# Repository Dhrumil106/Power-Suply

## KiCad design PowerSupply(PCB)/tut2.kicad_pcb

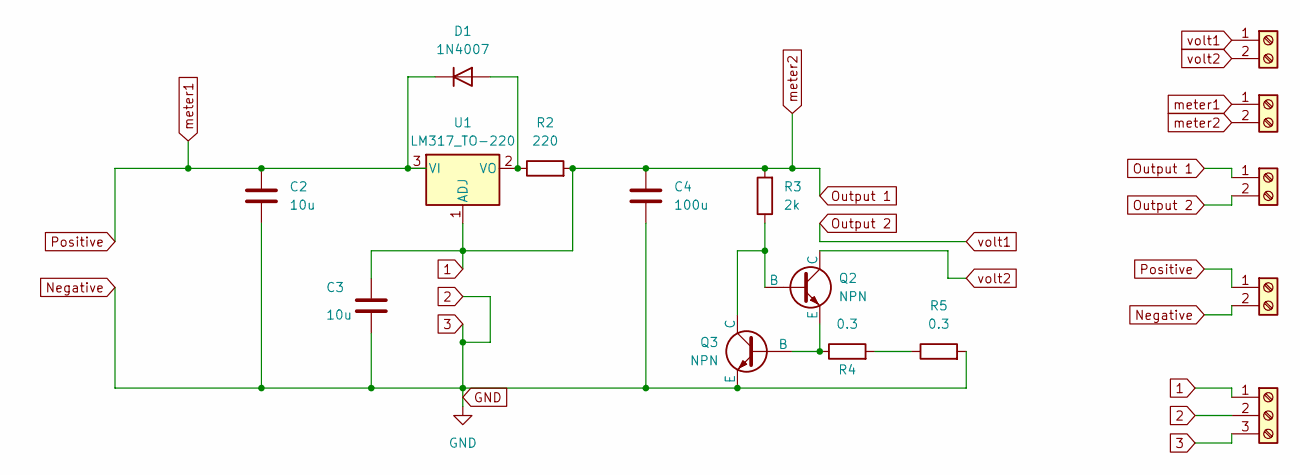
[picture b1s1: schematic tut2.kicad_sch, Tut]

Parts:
C2, C3: 10u; C_Radial_D5.0mm_H11.0mm_P2.00mm
C4: 100u; C_Radial_D8.0mm_H11.5mm_P3.50mm
D1: 1N4007; D_DO-41_SOD81_P7.62mm_Horizontal
J1: Screw_Terminal_01x03; TerminalBlock_Xinya_XY308-2.54-3P_1x03_P2.54mm_Horizontal
J2, J3, J4, J5: Screw_Terminal_01x02; TerminalBlock_Xinya_XY308-2.54-2P_1x02_P2.54mm_Horizontal
Q2, Q3: NPN; TO-92
R2: 220; R_Axial_DIN0207_L6.3mm_D2.5mm_P7.62mm_Horizontal
R3: 2k; R_Axial_DIN0207_L6.3mm_D2.5mm_P7.62mm_Horizontal
R4, R5: 0.3; R_Axial_DIN0207_L6.3mm_D2.5mm_P7.62mm_Horizontal
U1: LM317_TO-220; TO-220-3_Vertical

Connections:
1: C3.1, C4.1, J1.1, J2.1, J4.2, R2.2, R3.2, U1.1 (ADJ)
2: C2.2, C3.2, C4.2, J1.2, J1.3, J3.2, Q3.3 (E), R5.2
unnamed: D1.2 (A), R2.1, U1.2 (VO)
unnamed: Q2.2 (B), Q3.1 (C), R3.1
unnamed: Q2.3 (E), Q3.2 (B), R4.1
unnamed: R4.2, R5.1
Output 2: J2.2, J5.1
Positive: C2.1, D1.1 (K), J3.1, J4.1, U1.3 (VI)
volt2: J5.2, Q2.1 (C)

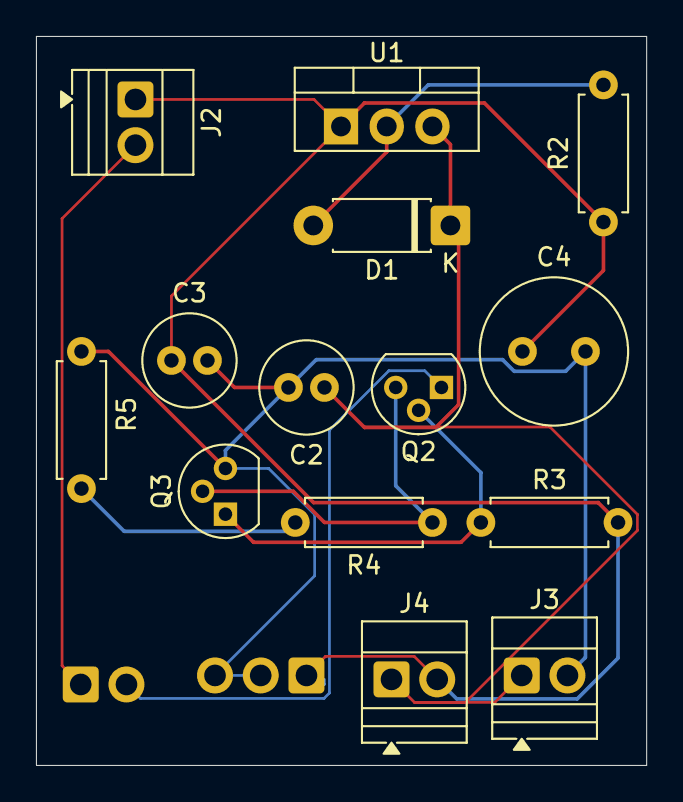
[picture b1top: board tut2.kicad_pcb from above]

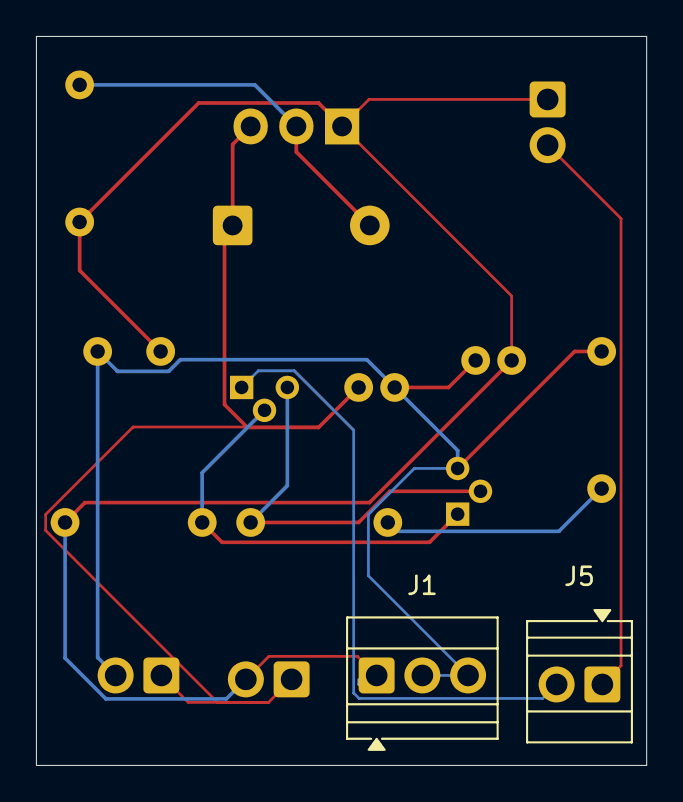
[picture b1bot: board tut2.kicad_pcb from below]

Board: 2 copper layers, 33.9 x 40.5 mm, 16 parts (2 on the bottom side), 9 nets.

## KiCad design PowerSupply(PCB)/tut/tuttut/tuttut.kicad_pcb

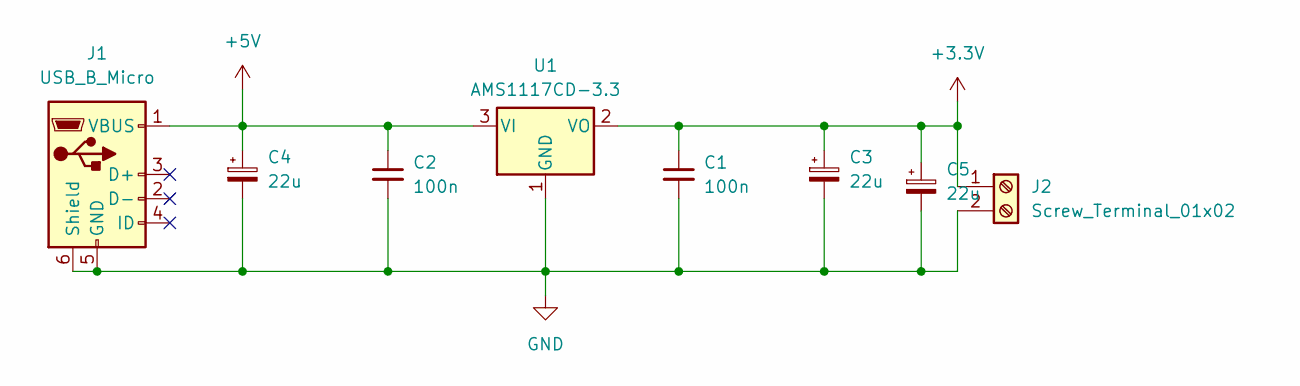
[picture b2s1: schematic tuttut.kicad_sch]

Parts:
C1, C2: 100n; C_0402_1005Metric
C3, C4, C5: 22u; CP_Elec_6.3x7.7
J1: USB_B_Micro; USB_Micro-B_Molex_47346-0001
J2: Screw_Terminal_01x02; TerminalBlock_Phoenix_MKDS-3-2-5.08_1x02_P5.08mm_Horizontal
U1: AMS1117CD-3.3; TO-252-3_TabPin2

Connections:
+3.3V: C1.1, C3.1, C5.1, J2.1, U1.2 (VO)
+5V: C2.1, C4.1, J1.1 (VBUS), U1.3 (VI)
GND: C1.2, C2.2, C3.2, C4.2, C5.2, J1.5 (GND), J1.6 (Shield), J2.2, U1.1 (GND)

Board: 2 copper layers, 8 parts (0 on the bottom side), 3 nets, no tracks yet.
